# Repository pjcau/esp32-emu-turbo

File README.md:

# ESP32 Emu Turbo

Handheld retro gaming console based on ESP32-S3 — **SNES** (primary) and **NES** (secondary) emulation.

## Project Goal

Build a portable battery-powered device based on ESP32-S3, capable of loading and playing retro games via SD card, with USB-C charging and an ILI9488 3.95" color LCD display.

## Where the project stands (2026-09-27)

- **The first article works.** Board v4.9.0 (article 0003, JLCPCB-assembled) passed
  every bring-up stage on 2026-09-11: USB power, rails, boot, display, SD, audio, all
  12 buttons, and **battery**.
- **15 systems run on the board.** NES, GB/GBC, SMS/GG/SG-1000, PC Engine, Genesis,
  Neo Geo Pocket, Colecovision at full speed; SNES at real speed
  (all but Mario Kart); DOOM at its 35 fps engine rate; Duke Nukem 3D playable
  (~50 fps in game); Wolfenstein 3D at 62 fps; arcade via a MAME 0.37 port (Pac-Man, 1942, 1943, Blood Bros.,
  Aero Fighters).
- **The board is driven from the host.** `scripts/board_ctl.py` launches ROMs,
  presses buttons, saves/loads states, captures audio and reads the profiling
  counters over the USB console; `scripts/emu_check.py` runs every core in one pass.
- **No board defect found.** Findings R37 (J4 contact face), R38 (no PDM filter) and
  R39 (pin-name swap) are closed in firmware or deferred to the next board. One open
  audio item: a low buzz at the drawn frame rate, analog, under investigation
  ([remediation/audio](website/docs/remediation/audio.md)).

Details: [first-boot session log](docs/first-boot-session-2026-08-29.md).

## Development Phases

### Phase 1 — Feasibility Analysis ✅
- Evaluate ESP32-S3 capabilities for SNES/NES emulation
- Select components (display, controller, power supply)

### Phase 2 — Hardware Design ✅
- KiCad electrical schematics (7 hierarchical sheets)
- OpenSCAD 3D enclosure model
- GPIO pin mapping and validation
- Docker rendering pipeline
- 4-layer PCB layout (160x75mm, JLCPCB-ready)

### Phase 3 — PCB Fabrication and First Article ✅
- Production files in `release_jlcpcb/` (current set **v4.9.0**: Gerber ZIP + BOM + CPL)
- All pre-production gates green (`make verify-all`): DFM, DFA, DRC, power-net integrity, JLCDFM
- First article (article 0003) assembled by JLCPCB and commissioned 2026-08-29 → 2026-09-11:
  bring-up firmware GREEN 53/0/6, stages 0–5 all PASS including battery
- Bench rules learned the hard way: unplug J3 for any flash/serial session from a
  laptop USB port (the IP5306 charge current collapses a 500 mA port); a freshly
  connected cell needs one USB "kick" before the IP5306 wakes from the switch
- v2 backlog: R37 top-contact J4, R38 PDM RC filter, J3 "+" and SPK polarity silkscreen

### Phase 4 — Software

Firmware = our [Retro-Go](https://github.com/ducalex/retro-go) fork (`retro-go/`
submodule). Per-step tables and measurements live in the docs:
[firmware](website/docs/software/firmware.md),
[emulators: tests and speed](website/docs/software/emulators.md),
[optimizations](website/docs/software/optimizations.md),
[emulator remediation](website/docs/remediation/emulators.md).

| Step | What | Status |
|:---|:---|:---|
| 4.1 | Hardware validation firmware (`software/`): display, SD, buttons, PDM audio | ✅ (IP5306 I2C not routed — N/A) |
| 4.2 | Retro-Go target: ILI9488 i80 driver, 480×320 scaler, 12-button input, PDM audio, Docker build | ✅ first boot 2026-09-12 |
| 4.3 | Retro-Go cores: NES, GB, GBC, SMS, GG, SG-1000, PCE, Genesis (YM2612 on core 1) | ✅ 60 fps |
| 4.4 | New cores: Neo Geo Pocket (`retro-extra`), Colecovision, DOOM (Freedoom), Duke Nukem 3D (`duke3d-go`), Wolfenstein 3D (`wolf3d-go`, 62 fps), Quake (`quake-go`, built) | ✅ on the board 2026-09-21 → 09-27 |
| 4.5 | Arcade: MAME 0.37b5 port (`mame-go`), ROMs in a 4 MB flash partition, tile cache, save states, 68000 idle-loop speed-ups | ✅ 8-bit boards 60 fps; Blood Bros. 60, Aero Fighters 47–57 |
| 4.6 | SNES renderer (Milestone A): 60 emulated fps on SMW, Zelda, Mega Man X, Super Metroid, DKC | ✅ Mario Kart 60 since 2026-09-28 (S-DSP on core 1) |
| 4.7 | Audio: every core at 32 kHz on the PDM sink, heavy chips at 16 kHz doubled, carrier off when silent | ✅ buzz at frame rate open |
| 4.8 | Launcher: GAME BRO! boot splash, art for new systems from [es-theme-gbz35](https://github.com/rxbrad/es-theme-gbz35) | ✅ |
| 4.9 | Host bench tools: `board_ctl.py`, `emu_check.py`, `snes_bench.py`, audio capture, Debug HUD | ✅ |
| 4.10 | Open: DOOM heap leak, GBA at 60 fps on the heavy games | ⏳ |

SNES, renderer cost per drawn frame (`scripts/snes_bench.py`, baseline → now):

| Scene | R (ms) | fps emulated / drawn |
|:---|---:|:---|
| Super Mario World (map / level) | 18.2 → 16.4 / 14.8 | 60 / 26 |
| Zelda: A Link to the Past | 24.9 → 9.5 | 60 / 25 |
| Mega Man X | 12.9 → 10.9 | 60 / 24 |
| Super Metroid (Mode 7) | 24.6 → 14.4 | 60 / 22 |
| Donkey Kong Country | 16.1 → 11.6 | 60 / 19 |
| Super Mario Kart (Mode 7 + DSP-1) | 22.5 → 22.5 | 57 / 11 |

### Phase 5 — Final Version (v2)
- Respin with the first-article backlog (R37 + silkscreen) and an I2S amplifier in place of the PDM audio chain (no audio coprocessor — the second ESP32-S3 core covers it)
- 3D-printed enclosure
- Final assembly

## PCB Design

| Parameter          | Value                                |
| ------------------ | ------------------------------------ |
| **Dimensions**     | 160 x 75 mm                          |
| **Layers**         | 4 (Signal / GND / Power / Signal)    |
| **Surface Finish** | ENIG                                 |
| **Assembly**       | JLCPCB PCBA (BOM + CPL in `release_jlcpcb/`) |
| **Trace Shorts**   | 0 (verified)                         |
| **Zone Fill**      | ✅ Inner layers filled (GND + 3V3/5V) |
| **Release**        | v4.9.0 — first article passed bring-up 2026-09-11 |
| **Estimated Cost** | ~$40/board (5 pcs, fully assembled)  |

## Key Requirements

| Component     | Specification                                                    |
| ------------- | ---------------------------------------------------------------- |
| **MCU**       | ESP32-S3 N16R8 (16MB flash, 8MB Octal PSRAM)                     |
| **Display**   | ILI9488 3.95" 320x480, 8-bit 8080 parallel, bare panel + 40P FPC |
| **Power**     | LiPo 3.7V 5000mAh + IP5306 (charger + boost) + SY8089 2A buck    |
| **Charging**  | USB-C (charge-and-play)                                          |
| **Audio**     | I2S PDM -> PAM8403 -> 28mm speaker                               |
| **Controls**  | 12 buttons (D-pad, ABXY, Start, Select, L, R)                    |
| **Storage**   | Micro SD card via SPI                                            |
| **Emulation** | SNES (primary), NES (secondary)                                  |

## Quick Start

### Clone (with submodules)

```bash
git clone --recurse-submodules https://github.com/pjcau/esp32-emu-turbo.git
cd esp32-emu-turbo

# If you already cloned without --recurse-submodules:
git submodule update --init --recursive
```

### Prerequisites

- **Python 3.12+**
- **KiCad 10** with `kicad-cli` (for local DRC/gerber export)
- **OrbStack** (lightweight Docker alternative, replaces Docker Desktop)

```bash
brew install --cask orbstack    # Container runtime (16x faster than Docker Desktop)
brew install --cask kicad       # Includes kicad-cli
```

### Generate hardware files

```bash
# Generate schematics (7 sheets + hierarchical root)
python3 -m scripts.generate_schematics hardware/kicad

# Generate PCB layout + JLCPCB exports
make generate-pcb

# Render PCB images (SVG + PNG + GIF)
make render-pcb

# Quick DFM check (1.4s, no Docker needed)
make verify-fast

# Full check pipeline: generate + DFM + DRC + gerbers + connectivity (~5s)
make fast-check

# Export Gerbers (local kicad-cli + Docker for zone fill only)
make export-gerbers-fast

# Full verification suite (DRC + simulation + consistency + short circuit)
make verify-all

# Export Gerbers with zone fill (all Docker)
make export-gerbers
```

### Render schematics and 3D model

```bash
# Build Docker images and render all assets
make render-all

# Or individually:
make render-schematics   # KiCad -> SVG
make render-enclosure    # OpenSCAD -> PNG
```

### Run documentation site locally

```bash
make website-dev
# or: cd website && npm start
```

## Project Structure

```
esp32-emu-turbo/
├── hardware/
│   ├── kicad/              # KiCad 10 schematics + PCB
│   │   ├── esp32-emu-turbo.kicad_sch   # Hierarchical root
│   │   ├── 01-power-supply.kicad_sch   # 7 sub-sheets
│   │   ├── ...
│   │   ├── esp32-emu-turbo.kicad_pcb   # PCB layout
│   │   └── jlcpcb/         # BOM + CPL for JLCPCB
│   └── enclosure/          # OpenSCAD parametric 3D model
├── release_jlcpcb/         # Production files for JLCPCB ordering
│   ├── gerbers/            # Gerber + drill files (22 layers)
│   ├── gerbers.zip         # Ready-to-upload ZIP
│   ├── bom.csv             # Bill of Materials (JLCPCB format)
│   ├── cpl.csv             # Component Placement List (65 parts)
│   └── bom-summary.md      # Human-readable BOM + cost estimate
├── retro-go/               # Retro-Go emulator (git submodule)
│   └── components/retro-go/targets/esp32-emu-turbo/  # Our target config
├── test-roms/              # Homebrew/public-domain test ROMs
│   ├── nes/ gb/ gbc/ sms/ gg/ pce/ gen/ snes/
│   └── README.md           # ROM sources and licenses
├── scripts/
│   ├── setup-sdcard.sh     # Format SD card + copy ROMs
│   ├── generate_schematics/ # Schematic generator (Python)
│   ├── generate_pcb/       # PCB layout generator (Python)
│   ├── render_pcba.sh      # Raytraced PCBA renders (only board imagery)
│   └── verify_schematic_pcb.py  # Consistency checker
├── docker/                 # Docker containers (KiCad + OpenSCAD)
├── website/                # Docusaurus documentation site
│   └── docs/               # All documentation pages
├── docker-compose.yml      # Hardware rendering containers
├── docker-compose.retro-go.yml  # Retro-Go build/flash containers
├── Makefile                # Top-level automation
└── CLAUDE.md               # AI assistant instructions
```

## Documentation

All project documentation lives in `website/docs/` and is published via Docusaurus to GitHub Pages:

- [Documentation Site](https://pjcau.github.io/esp32-emu-turbo/) — full docs online
- [Feasibility Analysis](website/docs/overview/feasibility.md)
- [SNES Hardware Spec](website/docs/overview/snes-hardware.md)
- [Bill of Materials](website/docs/design/components.md)
- [Electrical Schematics](website/docs/design/schematics.md)
- [PCB Design](website/docs/design/pcb.md)
- [Enclosure Design](website/docs/design/enclosure.md)
- [Manufacturing (JLCPCB)](website/docs/manufacturing/manufacturing.md)
- [First boot — staged session](website/docs/manufacturing/first-boot.md)
- [Software overview](website/docs/software/overview.md) · [Firmware](website/docs/software/firmware.md) · [Emulators](website/docs/software/emulators.md) · [Optimizations](website/docs/software/optimizations.md)

Engineering notes live in `docs/`:

- [**Known issues**](docs/known-issues.md) — what is still broken and what
  must not be "fixed". Re-derive the live state with `make open-issues`.
- [Waiver audit recovery](docs/archived/waiver-audit-recovery.md) — how the
  suppressions that could hide a dead board were retired.
- [Repository map](docs/REPO_MAP.md) — generated index of every script.

## 🤖 Claude Code Integration

This repository is also a **production-grade Claude Code skill suite** for KiCad + JLCPCB PCB design. All 43 skills used to design this PCB are available in `.claude/skills/`, and the 27 PCB-specific ones are packaged as the reusable `kicad-jlcpcb-skills` plugin.

### Install the plugin in your own project

```bash
# Inside Claude Code:
/plugin marketplace add pjcau/esp32-emu-turbo
/plugin install kicad-jlcpcb-skills
```

### What you get

- **27 PCB skills** — Design (5), Generate (7), Verify (11), Fix (4)
- **6 lifecycle slash commands** — `/design-pcb`, `/generate-pcb`, `/verify-pcb`, `/fix-pcb`, `/release-pcb`, `/bootstrap-new-pcb`
- **115 DFM tests + 9 DFA tests + 26 JLCPCB rules** (150 total manufacturing checks)
- **Pythonic KiCad generator** pipeline (no manual `.kicad_pcb` editing)
- **Deterministic, CI-friendly** workflow — full pipeline runs in ~5 seconds

### 5-phase design lifecycle

```
┌──────────┐   ┌──────────┐   ┌──────────┐   ┌──────────┐   ┌──────────┐
│  Design  │ → │ Generate │ → │  Verify  │ → │   Fix    │ → │ Release  │
└──────────┘   └──────────┘   └──────────┘   └──────────┘   └──────────┘
  5 skills       7 skills      11 skills      4 skills      shares Generate
```

### Documentation

- [`.claude/README.md`](.claude/README.md) — index of all 43 skills, 6 commands, 6 agents, 9 hooks
- [`docs/getting-started.md`](docs/getting-started.md) — install + first-run + first PCB walkthrough
- [`docs/lifecycle.md`](docs/lifecycle.md) — the 5-phase design lifecycle with exit criteria
- [`docs/skill-anatomy.md`](docs/skill-anatomy.md) — how to author your own skills on top of the base suite

### Credits

Plugin packaging (`.claude-plugin/`, lifecycle slash commands, flat `skills/` layout) is modeled on [addyosmani/agent-skills](https://github.com/addyosmani/agent-skills) — the first production-grade general-purpose Claude Code skill suite. If you want a non-hardware equivalent focused on SDLC workflows, go check it out. Our hardware-focused adaptation is fully complementary.

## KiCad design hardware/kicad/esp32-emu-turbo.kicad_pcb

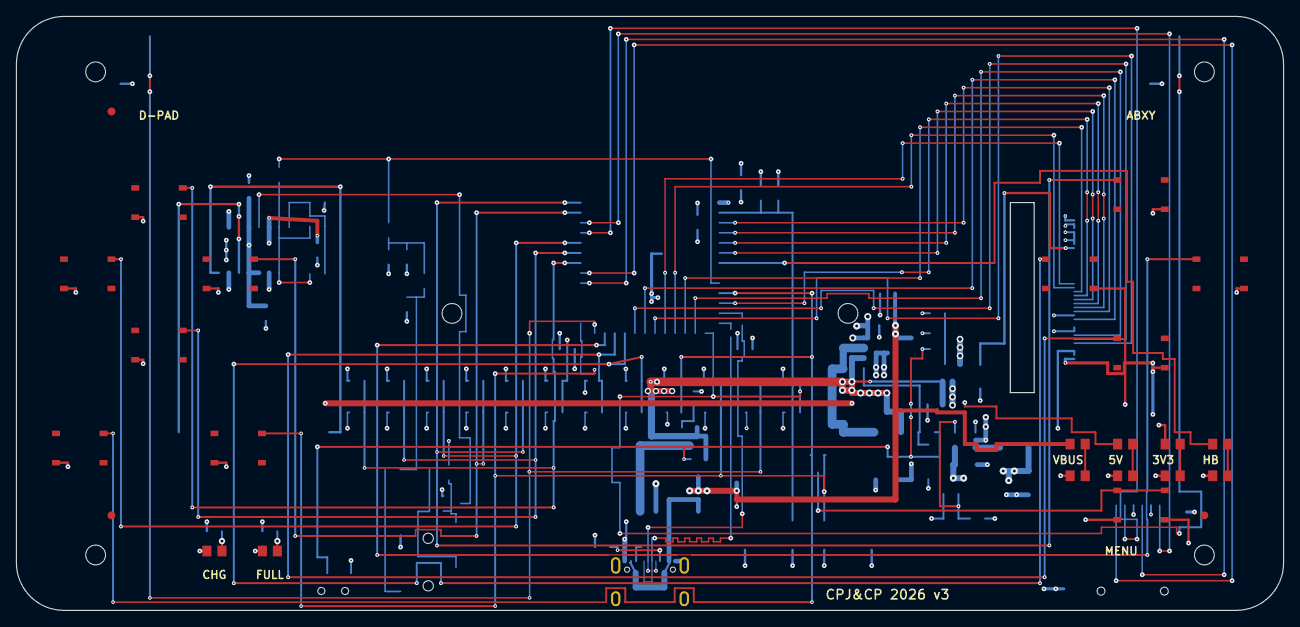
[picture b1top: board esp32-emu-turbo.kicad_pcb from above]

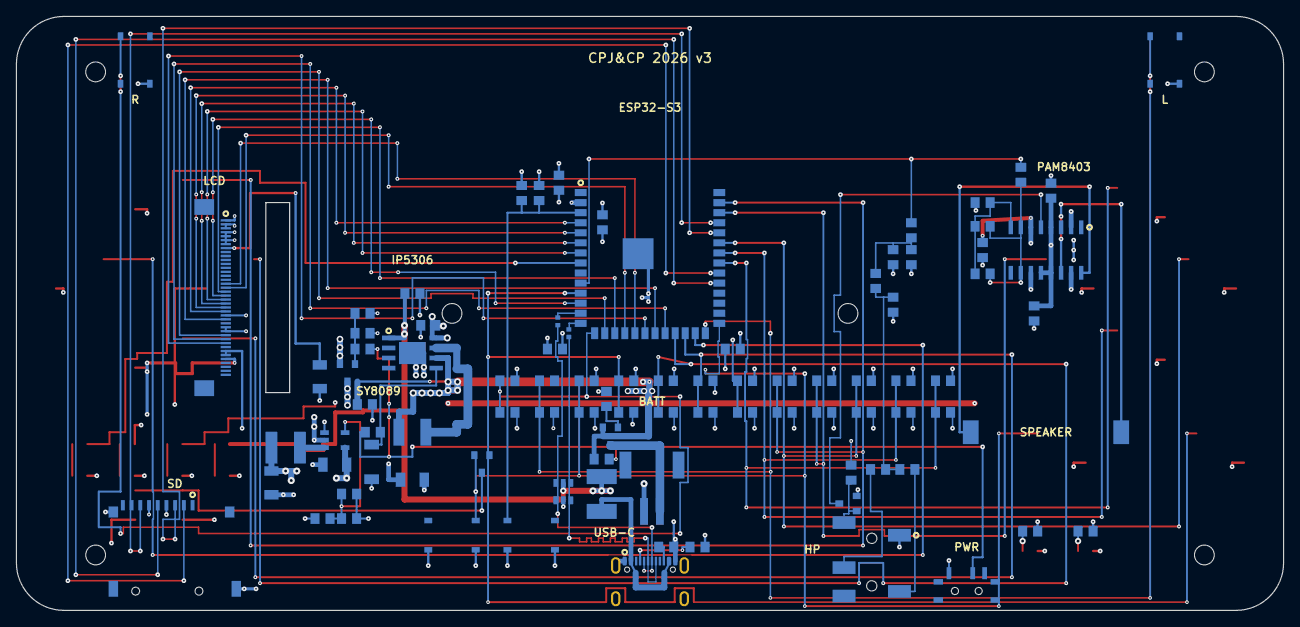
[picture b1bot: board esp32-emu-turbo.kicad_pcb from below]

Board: 4 copper layers, 160.0 x 75.0 mm, 115 parts (91 on the bottom side), 70 nets.

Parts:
C1, C19, C30: C_1206
C3, C4, C5, C6, C7, C8, C9, C10, C11, C12, C13, C14, C15, C16, C17, C18, C21, C22, C23, C24, C25, C26, C27, C28, C29, C31, C32, C33, C34, C35: C_0805
D1: SOT-23-3
F1: F_1812
FID1, FID2, FID3: Fiducial
J1: USB-C-16P
J3: JST-PH-2P-SMD
J4: FPC-40P-0.5mm
J5: PJ-327A
L1: SMD-4x4x2
L2: IND-SMD-4.0x4.0
LED1, LED2, LED3, LED4, LED5, LED6: LED_0805
Q1, Q2, Q3: SOT-23-3
R1, R2, R3, R4, R5, R6, R7, R8, R9, R10, R11, R12, R13, R14, R15, R17, R18, R20, R21, R24, R25, R26, R28, R29, R30, R31, R32, R33, R34, R35, R36, R37, R38, R39, R40: R_0805
R22, R23: R_0402
R27: R_1206
SPK1: Speaker-28mm
SW1, SW2, SW3, SW4, SW5, SW6, SW7, SW8, SW9, SW10, SW11, SW12, SW13, SW14, SW15: SW-SMD-5.1x5.1
SW16: SS-12D00G3
SW17: SW-SMD-2P-TS1088
U1: ESP32-S3-WROOM-1-N16R8
U2: ESOP-8
U3: SOT-23-5
U4: SOT-23-6
U5: SOP-16
U6: TF-01A

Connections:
+3V3: C3.1, C4.1, C26.1, C28.1, C29.1, C30.1, J4.2, J4.3, J4.28, J4.29, J4.34, J4.35, L2.1, R3.1, R4.2, R5.2, R6.2, R7.2, R8.2, R9.2, R10.2, R11.2, R12.2, R13.2, R15.2, R17.2, R18.2, R25.1, R30.2, R40.1, U1.2, U6.4
+5V: C1.1, C19.1, C23.1, C24.2, C25.1, Q2.3, R27.2, R29.2, U3.1, U3.4, U5.4, U5.6, U5.12, U5.13
+5V_VOUT: C27.2, C32.2, Q2.2, R32.2, U2.8
BAT+: C18.1, L1.1, Q1.2, R34.2, U2.6
BAT_IN: J3.1, Q1.3
BTN_A: C9.1, R8.1, SW5.1, U1.39
BTN_B: C10.1, R9.1, SW6.1, U1.25
BTN_DOWN: C6.1, R5.1, SW2.2, U1.34
BTN_L: C15.1, R14.1, SW11.3, U1.26
BTN_LEFT: C7.1, R6.1, SW3.2, U1.35
BTN_R: C16.1, R15.1, SW12.3, U1.15
BTN_RIGHT: C8.1, R7.1, SW4.2, U1.38
BTN_SELECT: C14.1, D1.2, R13.1, SW10.2, SW14.2, SW16.4b, SW16.4d, U1.27
BTN_START: C13.1, D1.1, R12.1, SW9.2, U1.11
BTN_UP: C5.1, R4.1, SW1.2, U1.33
BTN_X: C11.1, R10.1, SW7.1, U1.24
BTN_Y: C12.1, R11.1, SW8.1, U1.23
BUCK_FB: C29.2, R25.2, R26.1, U3.5
BUCK_LX: L2.2, U3.3
EN: C31.2, R3.2, SW15.1, U1.3
GND: C1.2, C3.2, C4.2, C5.2, C6.2, C7.2, C8.2, C9.2, C10.2, C11.2, C12.2, C13.2, C14.2, C15.2, C16.2, C17.2, C18.2, C19.2, C21.1, C23.2, C24.1, C25.2, C26.2, C27.1, C28.2, C30.2, C31.1, C34.2, J1.1, J1.12, J1.13, J1.14, J3.2, J4.1, J4.4, J4.5, J4.6, J4.7, J4.25, J4.36, J5.2, LED1.1, LED2.1, LED3.1, LED4.1, LED5.1, LED6.1, Q3.2, R1.2, R2.2, R24.2, R26.2, R36.2, R39.2, SW1.3, SW2.3, SW3.3, SW4.3, SW5.4, SW6.4, SW7.4, SW8.4, SW9.3, SW10.3, SW11.2, SW12.2, SW13.3, SW13.4, SW14.3, SW14.4, SW15.3, SW15.4, SW16.1, SW17.2, U1.41, U2.EP, U3.2, U4.2, U5.2, U5.11, U5.15, U6.6, U6.10, U6.12
HP_AC: C35.2, R37.1, R38.1, R39.1
HP_FILT: C34.1, C35.1, R35.2, R36.1
HP_L: J5.3, R37.2
HP_R: J5.5, R38.2
I2S_DOUT: C22.1, R35.1, U1.10
IP5306_KEY: C33.2, SW17.1, U2.5
JACK_DET: J5.6, Q3.1, R40.2
LCD_CS: J4.32, U1.20
LCD_D0: J4.24, U1.4
LCD_D1: J4.23, U1.5
LCD_D2: J4.22, U1.6
LCD_D3: J4.21, U1.7
LCD_D4: J4.20, U1.12
LCD_D5: J4.19, U1.17
LCD_D6: J4.18, U1.18
LCD_D7: J4.17, U1.19
LCD_DC: J4.31, U1.22
LCD_RST: J4.26, U1.21
LCD_WR: J4.30, U1.16
LED1_RA: LED1.2, R17.1
LED2_RA: LED2.2, R18.1
LED3_RA: LED3.2, R28.1
LED4_RA: LED4.2, R29.1
LED5_RA: LED5.2, R30.1
LED6_RA: LED6.2, R31.1
LED_BLA: J4.8, R27.1
LED_HB: R31.2, U1.8
LX: L1.2, U2.7
MENU_K: D1.3, SW13.1, SW13.2
PAM_IN_AC: C22.2, R20.2, R21.2, U5.7, U5.10
PAM_MUTE: Q3.3, U5.5
PAM_VREF: C21.2, R20.1, R21.1, U5.8
PWR_SW: C33.1, R33.2, R34.1, SW16.2
PWR_SW_GATE: C32.1, Q2.1, R32.1, R33.1
RPP_GATE: Q1.1, R24.1
SD_CLK: U1.31, U6.5
SD_CS: U1.32, U6.2
SD_MISO: U1.37, U6.7, U6.8
SD_MOSI: U1.36, U6.3
SPK+: SPK1.1, U5.16
SPK-: SPK1.2, U5.14
USB_CC1: J1.4, R1.1
USB_CC2: J1.10, R2.1
USB_D+: J1.6, J1.8, R22.2, U4.3, U4.4
USB_D-: J1.5, J1.7, R23.2, U4.1, U4.6
USB_DM_MCU: R23.1, U1.13
USB_DP_MCU: R22.1, U1.14
VBUS: C17.1, F1.2, R28.2, U2.1, U4.5
VBUS_IN: F1.1, J1.2, J1.11

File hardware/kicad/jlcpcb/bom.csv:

Comment,Designator,Footprint,LCSC Part #,Quantity
ESP32-S3-WROOM-1-N16R8,U1,Module_ESP32-S3-WROOM-1,C2913202,1
IP5306,U2,ESOP-8,C181692,1
SY8089AAAC 2A Buck,U3,SOT-23-5,C78988,1
PAM8403,U5,SOP-16,C5122557,1
USB-C 16-pin,J1,USB-C-SMD-16P,C2765186,1
Micro SD Card Slot,U6,TF-01A,C91145,1
JST PH 2-pin SMD,J3,JST-PH-2P-SMD,C295747,1
Red LED 0805,LED1,LED_0805,C84256,1
Red LED 0805,LED2,LED_0805,C19171391,1
1uH 4.5A Inductor,L1,SMD-4x4x2mm,C280579,1
2.2uH 2.95A Inductor,L2,IND-SMD-4.0x4.0,C36409,1
5.1k 0805,"R1,R2",R_0805,C27834,2
10k 0805,"R3,R4,R5,R6,R7,R8,R9,R10,R11,R12,R13,R15",R_0805,C17414,12
20k 0805,"R20,R21",R_0805,C4328,2
100k 0805,"R24,R25",R_0805,C149504,2
22k 0805,"R26,R32",R_0805,C17560,2
22pF 0805 C0G,C29,C_0805,C1804,1
1k 0805,"R17,R18,R33",R_0805,C17513,3
100nF 0805,"C3,C4,C5,C6,C7,C8,C9,C10,C11,C12,C13,C14,C15,C16,C21,C26,C31",C_0805,C49678,17
0.47uF 0805,C22,C_0805,C13967,1
1uF 0805,"C23,C24,C25,C32,C33",C_0805,C28323,5
10uF 0805,"C17,C18,C27",C_0805,C15850,3
22uF 1206 MLCC,"C1,C19,C30",C_1206,C12891,3
SMT Tact Switch 5.1x5.1mm,"SW1,SW2,SW3,SW4,SW5,SW6,SW7,SW8,SW9,SW10,SW11,SW12,SW13,SW15,SW14",SW-SMD-5.1x5.1,C318884,15
FPC 40-pin 0.5mm Bottom Contact,J4,FPC-40P-0.5mm,C2856812,1
Slide Switch SS-12D00G3,SW16,SS-12D00G3,C431540,1
USBLC6-2SC6 USB ESD TVS,U4,SOT-23-6,C7519,1
22R 0402,"R22,R23",R_0402,C25092,2
20R 1206,R27,R_1206,C17955,1
PTC Resettable Fuse 2A 1812,F1,F_1812,C960026,1
BAT54C Dual Schottky Diode,D1,SOT-23,C37704,1
SI2301CDS P-Channel MOSFET,"Q1,Q2",SOT-23,C10487,2
"Red LED 0805 (bring-up diagnostic, DNP in production)","LED3,LED4,LED5,LED6",LED_0805,C19171391,4
"5.1k 0805 (bring-up diagnostic, DNP in production)","R28,R29",R_0805,C27834,2
"1k 0805 (bring-up diagnostic, DNP in production)","R30,R31",R_0805,C17513,2
1M 0805,R34,R_0805,C17514,1
"SMD Momentary Switch 3.9x3.0mm TS-1088 (DO NOT PLACE - manual IP5306 KEY wake, fit only if the C33 RC needs it)",SW17,SW-SMD-2P-TS1088,C720477,1

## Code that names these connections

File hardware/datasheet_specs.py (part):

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            "2":  {"net": _exact("+3V3"),       "function": "3V3 power supply", "type": "smd"},
            # Pin 3 (EN) — connected via pull-up resistor trace, may not show in pad net
            "3":  {"net": _any_of("EN", ""),    "function": "EN (chip enable, via pull-up)", "type": "smd"},
            "4":  {"net": _exact("LCD_D0"),     "function": "GPIO4 — LCD data bus D0", "type": "smd"},
            "5":  {"net": _exact("LCD_D1"),     "function": "GPIO5 — LCD data bus D1", "type": "smd"},
            "6":  {"net": _exact("LCD_D2"),     "function": "GPIO6 — LCD data bus D2", "type": "smd"},
            "7":  {"net": _exact("LCD_D3"),     "function": "GPIO7 — LCD data bus D3", "type": "smd"},
            # GPIO15/16: the I2S_BCLK/I2S_LRCK net reservation was retired
            # 2026-07-26 (R10-LOW-2) — audio is PDM TX, .clk = I2S_GPIO_UNUSED,
            # only DOUT is used. GPIO15 was then taken by the diagnostic
            # heartbeat LED (workstream H): unlike the retired I2S labels, it
            # is a real two-pin circuit, U1.8 -> R31 -> LED6 -> GND. GPIO16
            # stays unconnected and free for v2 (ADC2).
            "8":  {"net": _exact("LED_HB"),     "function": "GPIO15 — diagnostic heartbeat LED (R31/LED6)", "type": "smd"},
            "9":  {"net": _unconnected(),       "function": "GPIO16 — unused, free for v2 (I2S reservation retired)", "type": "smd"},
            "10": {"net": _exact("I2S_DOUT"),   "function": "GPIO17 — I2S data out", "type": "smd"},
            "11": {"net": _exact("BTN_START"),  "function": "GPIO18 — Start button", "type": "smd"},
            "12": {"net": _exact("LCD_D4"),     "function": "GPIO8 — LCD data bus D4", "type": "smd"},
            "13": {"net": _exact("USB_DM_MCU"), "function": "GPIO19 — USB D- (after 22Ω R23)", "type": "smd"},
            "14": {"net": _exact("USB_DP_MCU"), "function": "GPIO20 — USB D+ (after 22Ω R22)", "type": "smd"},
            "15": {"net": _exact("BTN_R"),      "function": "GPIO3 — R shoulder button", "type": "smd"},
            "16": {"net": _exact("LCD_WR"),     "function": "GPIO46 — LCD write strobe", "type": "smd"},
            "17": {"net": _exact("LCD_D5"),     "function": "GPIO9 — LCD data bus D5", "type": "smd"},
            "18": {"net": _exact("LCD_D6"),     "function": "GPIO10 — LCD data bus D6", "type": "smd"},
            "19": {"net": _exact("LCD_D7"),     "function": "GPIO11 — LCD data bus D7", "type": "smd"},
            "20": {"net": _exact("LCD_CS"),     "function": "GPIO12 — LCD chip select", "type": "smd"},
            "21": {"net": _exact("LCD_RST"),    "function": "GPIO13 — LCD reset", "type": "smd"},
            "22": {"net": _exact("LCD_DC"),     "function": "GPIO14 — LCD data/command", "type": "smd"},
            "23": {"net": _exact("BTN_Y"),      "function": "GPIO21 — Y button", "type": "smd"},
            "24": {"net": _exact("BTN_X"),      "function": "GPIO47 — X button", "type": "smd"},
            "25": {"net": _exact("BTN_B"),      "function": "GPIO48 — B button", "type": "smd"},
            "26": {"net": _exact("BTN_L"),      "function": "GPIO45 — L shoulder button", "type": "smd"},
            "27": {"net": _exact("BTN_SELECT"), "function": "GPIO0 — Select button (also BOOT)", "type": "smd"},
            "28": {"net": _unconnected(),       "function": "GPIO35 — Octal SPI PSRAM (N/A)", "type": "smd"},
            "29": {"net": _unconnected(),       "function": "GPIO36 — Octal SPI PSRAM (N/A)", "type": "smd"},
            "30": {"net": _unconnected(),       "function": "GPIO37 — Octal SPI PSRAM (N/A)", "type": "smd"},
            "31": {"net": _exact("SD_CLK"),     "function": "GPIO38 — SD card clock", "type": "smd"},
            "32": {"net": _exact("SD_CS"),      "function": "GPIO39 — SD card chip select", "type": "smd"},
            "33": {"net": _exact("BTN_UP"),     "function": "GPIO40 — D-pad up", "type": "smd"},
            "34": {"net": _exact("BTN_DOWN"),   "function": "GPIO41 — D-pad down", "type": "smd"},
            "35": {"net": _exact("BTN_LEFT"),   "function": "GPIO42 — D-pad left", "type": "smd"},
            "36": {"net": _exact("SD_MOSI"),    "function": "GPIO44 (U0RXD) — SD MOSI", "type": "smd"},
            "37": {"net": _exact("SD_MISO"),    "function": "GPIO43 (U0TXD) — SD MISO", "type": "smd"},
            "38": {"net": _exact("BTN_RIGHT"),  "function": "GPIO2 — D-pad right", "type": "smd"},
            "39": {"net": _exact("BTN_A"),      "function": "GPIO1 — A button", "type": "smd"},
            # Pin 40 is GND — connected via copper zone fill, not direct pad net
            "40": {"net": _any_of("GND", ""),   "function": "GND (bottom pad row, zone-filled)", "type": "smd"},
            "41": {"net": _exact("GND"),        "function": "EPAD — exposed ground pad", "type": "smd"},
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        "datasheet_page": 0,
        "pins": {
            "1": {"net": _exact("+3V3"),     "function": "Output side — +3V3 rail / C30", "type": "smd"},
            "2": {"net": _exact("BUCK_LX"),  "function": "Switch side — U3 pin 3 (LX)", "type": "smd"},
        },
    },

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    # We use mono (RIGHT channel wired to speaker): INL=INR=PAM_IN_AC
    # (both tied to the single PDM data line through the C22 DC-block).
    # C22 is a SERIES cap, so its two terminals are two distinct nets:
    #   ESP32 GPIO17 --I2S_DOUT--> C22.1 || C22.2 --PAM_IN_AC--> U5.7/U5.10
    # Do NOT label the PAM side "I2S_DOUT": that made DRC report a
    # permanent phantom "unconnected" on I2S_DOUT.
    # OUTR+ → SPK+, OUTR- → SPK- (BTL output on the right-channel pair).
    # OUTL+/OUTL- are left floating — PAM8403 datasheet app note allows
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    # 3 signal pins + 2 shell NPTHs
    # Circuit diagram: pin 2 is common, connects to 1 or 3 based on position
    #
    # SW16 RESPIN (2026-08-03): pin 2 is the gate control node PWR_SW, not
    # a dead stub on BAT+. Slid toward pin 1 (east, board interior) the
    # common is shorted to GND, PWR_SW goes to 0 V and Q2 turns the whole
    # +5V load rail on. Slid the other way the common lands on pin 3,
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
    # ======================================================================
    # SW14 — Tact Switch for Boot/Select (C318884)
    # Dual purpose: GPIO0/BTN_SELECT during runtime, BOOT during programming
    # ======================================================================
    "SW14": {
        "component": "Tact Switch (Boot/Select)",
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        "datasheet": "SW1-SW13_Tact-Switch_C318884.pdf",
        "datasheet_page": 1,
        "pins": {
            "1": {"net": _unconnected(),         "function": "BTN_SELECT (shorted to pin 2, may not have net)", "type": "smd"},
            "2": {"net": _exact("BTN_SELECT"),   "function": "BTN_SELECT / GPIO0 (BOOT)", "type": "smd"},
            "3": {"net": _exact("GND"),          "function": "GND (internally shorted to pin 4)", "type": "smd"},
            "4": {"net": _exact("GND"),          "function": "GND (shorted to pin 3)", "type": "smd"},
        },
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    ("R28", "LED3", "5.1k", "C27834", "VBUS",   "VBUS present, F1 fuse intact"),
    ("R29", "LED4", "5.1k", "C27834", "+5V",    "IP5306 boost alive"),
    ("R30", "LED5", "1k",   "C17513", "+3V3",   "buck alive, rail not shorted"),
    ("R31", "LED6", "1k",   "C17513", "LED_HB", "GPIO15 heartbeat / blink codes"),
]

for _r, _led, _val, _rlcsc, _rail, _why in _DIAG_BANK:
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    "pins": {
        "1": {"net": _exact("RPP_GATE"), "function": "Gate — pulled to GND via R24 (always ON)", "type": "smd"},
        "2": {"net": _exact("BAT+"),     "function": "Source — protected side, IP5306 BAT pin", "type": "smd"},
        "3": {"net": _exact("BAT_IN"),   "function": "Drain — battery connector side (J3 pin 1); body diode blocks a reversed cell", "type": "smd"},
    },
}

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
